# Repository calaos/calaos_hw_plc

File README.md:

# Intro

Calaos IO is an electronic board designed to controlled as many I/O as possible. It's intented to replace the wago IO modules in a house. It takes places in the electronic board.
Calaos IO is currently in design phase, and it's far to be complete

Look at calaos Wiki for more informations : http://www.calaos.fr/wiki/en/calaos_io_controller

This repository holds the documentation for the software and protocol parts

# doc

The doc foloder contains the state machine definitions and frame format.

# src/stm32

The src folder contains a prototype for an STM32 master on the RS485 bus
In order to build it, the gcc4mbed submodule must be initialized using 

    git submodule update --init
    
Then to fetch the toolchain:

    cd gcc4mbed
    ./linux_install
    
Note that the compiler should be added in your PATH to be used.

Finally go to the src folder and type

    make

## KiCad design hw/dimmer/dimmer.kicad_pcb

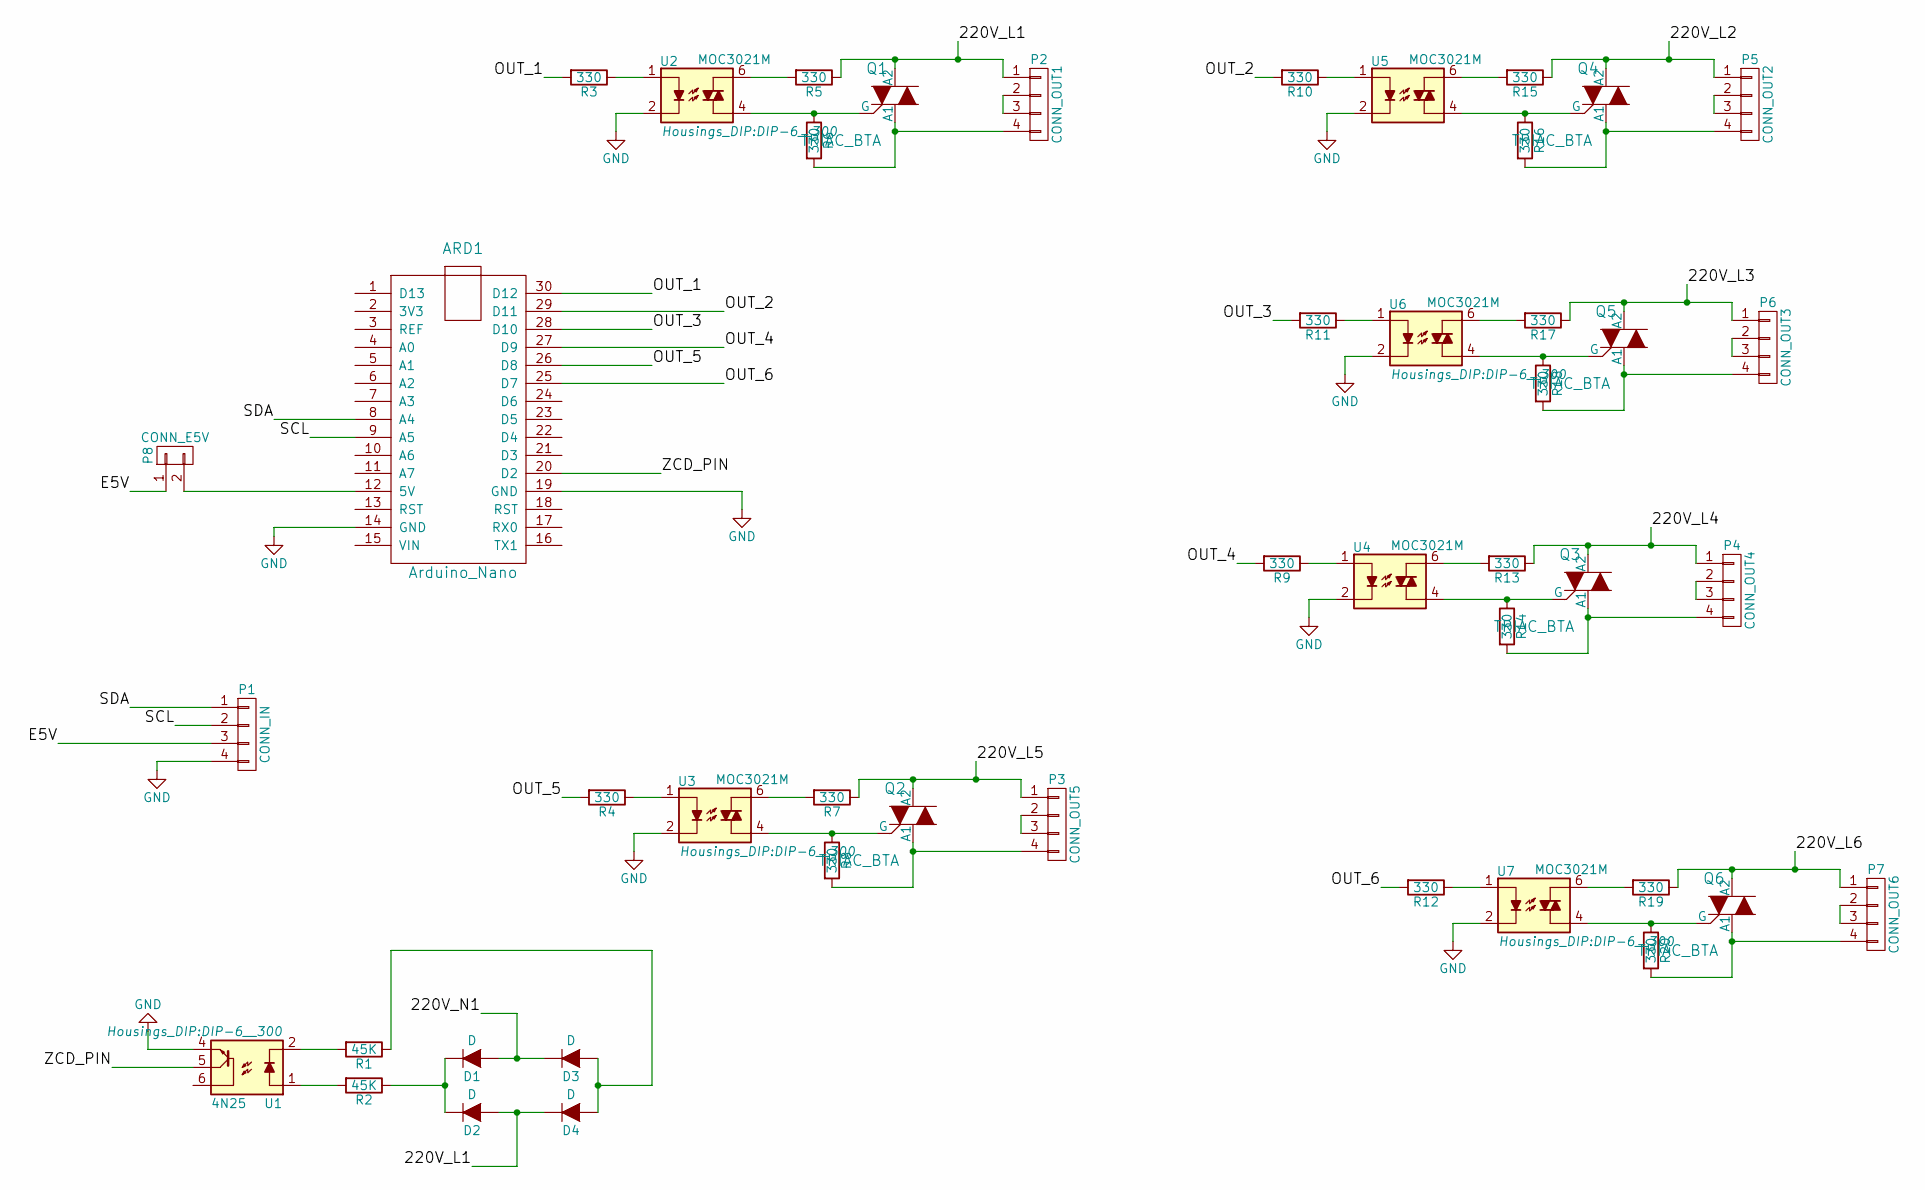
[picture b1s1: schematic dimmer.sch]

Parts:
ARD1: Arduino_Nano; arduino_nano_header
D1, D2, D3, D4: D; Diode_DO-35_SOD27_Horizontal_RM10
P1: CONN_IN; Pin_Header_Straight_1x04
P2: CONN_OUT1; mors_4p
P3: CONN_OUT5; mors_4p
P4: CONN_OUT4; mors_4p
P5: CONN_OUT2; mors_4p
P6: CONN_OUT3; mors_4p
P7: CONN_OUT6; mors_4p
P8: CONN_E5V; Pin_Header_Straight_1x02
Q1, Q2, Q3, Q4, Q5, Q6: TRIAC_BTA; TO-220
R1, R2: 45K; Resistor_Horizontal_RM10mm
R3, R4, R5, R6, R7, R8, R9, R10, R11, R12, R13, R14, R15, R16, R17, R18, R19, R20: 330; Resistor_Horizontal_RM10mm
U1: 4N25; DIP-6__300
U2, U3, U4, U5, U6, U7: MOC3021M; DIP-6__300

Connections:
/220V_L1: D2.1 (A), D4.2 (K), P2.1, Q1.2 (A2), R5.1
/220V_L2: P5.1, Q4.2 (A2), R15.1
/220V_L3: P6.1, Q5.2 (A2), R17.1
/220V_L4: P4.1, Q3.2 (A2), R13.1
/220V_L5: P3.1, Q2.2 (A2), R7.1
/220V_L6: P7.1, Q6.2 (A2), R19.1
/220V_N1: D1.1 (A), D3.2 (K)
/E5V: P1.3, P8.1
/OUT_1: ARD1.30 (D12), R3.2
/OUT_2: ARD1.29 (D11), R10.2
/OUT_3: ARD1.28 (D10), R11.2
/OUT_4: ARD1.27 (D9), R9.2
/OUT_5: ARD1.26 (D8), R4.2
/OUT_6: ARD1.25 (D7), R12.2
/SCL: ARD1.9 (A5), P1.2
/SDA: ARD1.8 (A4), P1.1
/ZCD_PIN: ARD1.20 (D2), U1.5
GND: ARD1.14 (GND), ARD1.19 (GND), P1.4, U1.4, U2.2, U3.2, U4.2, U5.2, U6.2, U7.2
unnamed: ARD1.12 (5V), P8.2
unnamed: D1.2 (K), D2.2 (K), R2.1
unnamed: D3.1 (A), D4.1 (A), R1.1
unnamed: P2.2, P2.3
unnamed: P2.4, Q1.3 (A1), R6.2
unnamed: P3.2, P3.3
unnamed: P3.4, Q2.3 (A1), R8.2
unnamed: P4.2, P4.3
unnamed: P4.4, Q3.3 (A1), R14.2
unnamed: P5.2, P5.3
unnamed: P5.4, Q4.3 (A1), R16.2
unnamed: P6.2, P6.3
unnamed: P6.4, Q5.3 (A1), R18.2
unnamed: P7.2, P7.3
unnamed: P7.4, Q6.3 (A1), R20.2
unnamed: Q1.1 (G), R6.1, U2.4
unnamed: Q2.1 (G), R8.1, U3.4
unnamed: Q3.1 (G), R14.1, U4.4
unnamed: Q4.1 (G), R16.1, U5.4
unnamed: Q5.1 (G), R18.1, U6.4
unnamed: Q6.1 (G), R20.1, U7.4
unnamed: R1.2, U1.2
unnamed: R2.2, U1.1
unnamed: R3.1, U2.1
unnamed: R4.1, U3.1
unnamed: R5.2, U2.6
unnamed: R7.2, U3.6
unnamed: R9.1, U4.1
unnamed: R10.1, U5.1
unnamed: R11.1, U6.1
unnamed: R12.1, U7.1
unnamed: R13.2, U4.6
unnamed: R15.2, U5.6
unnamed: R17.2, U6.6
unnamed: R19.2, U7.6

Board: 2 copper layers, 46 parts (0 on the bottom side), 53 nets, no tracks yet.

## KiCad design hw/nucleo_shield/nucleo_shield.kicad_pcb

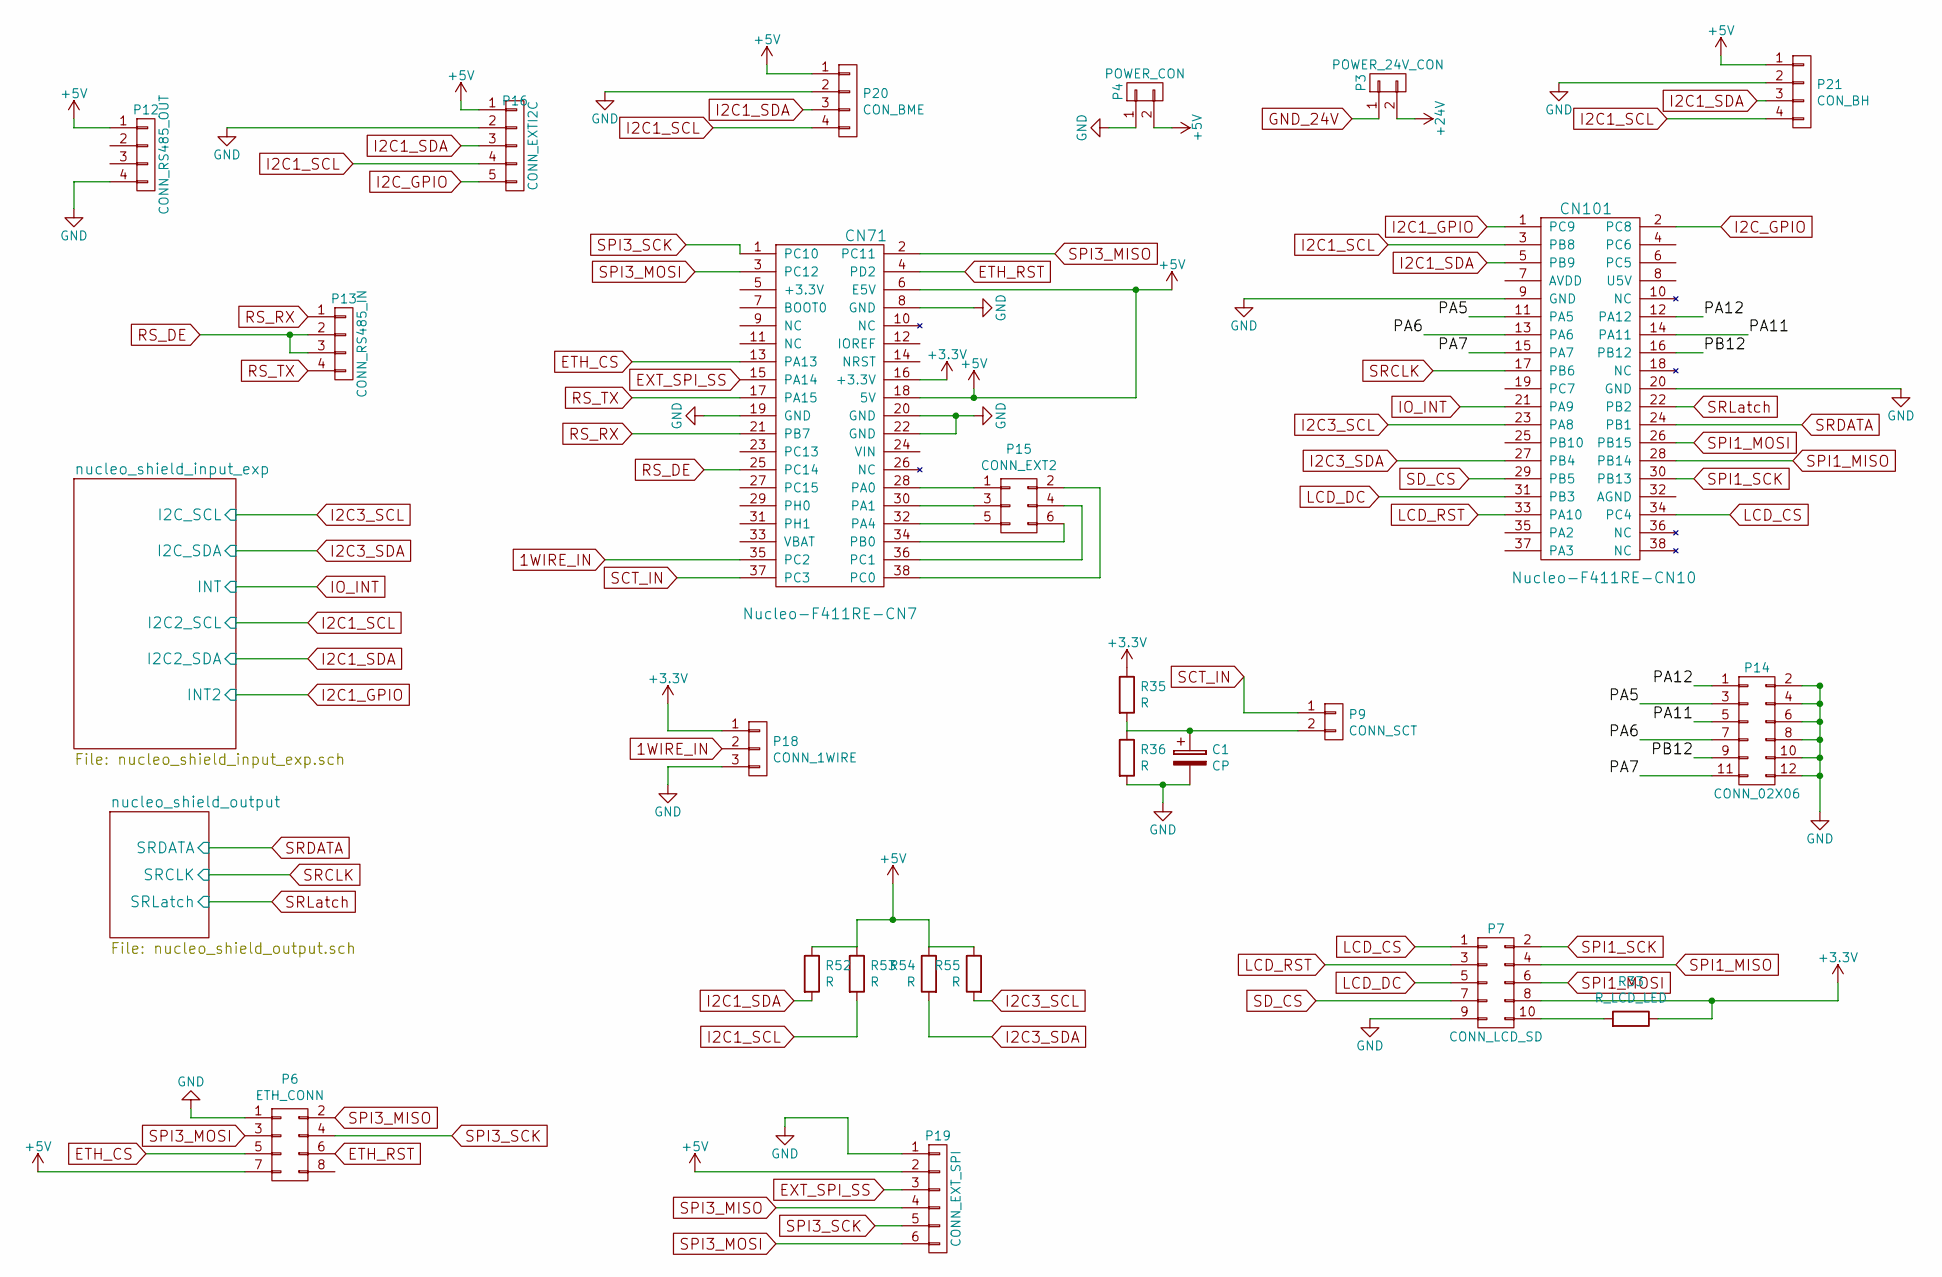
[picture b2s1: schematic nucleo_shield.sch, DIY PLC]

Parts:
C1: CP; C_Radial_D5_L11_P2
CN71: Nucleo-F411RE-CN7; Pin_Header_Straight_2x19
CN101: Nucleo-F411RE-CN10; Pin_Header_Straight_2x19
P3: POWER_24V_CON; mors_2p
P4: POWER_CON; mors_2p
P6: ETH_CONN; Pin_Header_Straight_2x04
P7: CONN_LCD_SD; Pin_Header_Straight_2x05
P9: CONN_SCT; Pin_Header_Straight_1x02
P12: CONN_RS485_OUT; Pin_Header_Straight_1x04
P13: CONN_RS485_IN; Pin_Header_Straight_1x04
P14: CONN_02X06; Pin_Header_Straight_2x06
P15: CONN_EXT2; Pin_Header_Straight_2x03
P16: CONN_EXTI2C; Pin_Header_Straight_1x05
P18: CONN_1WIRE; Pin_Header_Straight_1x03
P19: CONN_EXT_SPI; Pin_Header_Straight_1x06
P20: CON_BME; Pin_Header_Straight_1x04
P21: CON_BH; Pin_Header_Straight_1x04
R33: R_LCD_LED; R_0805_HandSoldering
R35, R36, R52, R53, R54, R55: R; R_0805_HandSoldering

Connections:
1WIRE_IN: CN71.35 (PC2), P18.2
+3V3: CN71.16 (+3.3V), P7.8, P18.1, R33.1, R35.1
+24V: P3.2; also elsewhere on the board
/PA5: CN101.11 (PA5), P14.3
/PA6: CN101.13 (PA6), P14.7
/PA7: CN101.15 (PA7), P14.11
/PA11: CN101.14 (PA11), P14.5
/PA12: CN101.12 (PA12), P14.1
/PB12: CN101.16 (PB12), P14.9
ETH_CS: CN71.13 (PA13), P6.5
ETH_RST: CN71.4 (PD2), P6.6
EXT_SPI_SS: CN71.15 (PA14), P19.3
GND: C1.2, CN71.8 (GND), CN71.19 (GND), CN71.20 (GND), CN71.22 (GND), CN101.9 (GND), CN101.20 (GND), P4.1, P6.1, P7.9, P12.4, P14.2, P14.4, P14.6, P14.8, P14.10, P14.12, P16.2, P18.3, P19.1, P20.2, P21.2, R36.2; also elsewhere on the board
GND_24V: P3.1; also elsewhere on the board
I2C1_GPIO: CN101.1 (PC9); also elsewhere on the board
I2C1_SCL: CN101.3 (PB8), P16.4, P20.4, P21.4, R53.2; also elsewhere on the board
I2C1_SDA: CN101.5 (PB9), P16.3, P20.3, P21.3, R52.2; also elsewhere on the board
I2C3_SCL: CN101.23 (PA8), R55.2; also elsewhere on the board
I2C3_SDA: CN101.27 (PB4), R54.2; also elsewhere on the board
I2C_GPIO: CN101.2 (PC8), P16.5
IO_INT: CN101.21 (PA9); also elsewhere on the board
LCD_CS: CN101.34 (PC4), P7.1
LCD_DC: CN101.31 (PB3), P7.5
LCD_RST: CN101.33 (PA10), P7.3
unnamed: C1.1, P9.2, R35.2, R36.1
unnamed: CN71.28 (PA0), P15.1
unnamed: CN71.30 (PA1), P15.3
unnamed: CN71.32 (PA4), P15.5
unnamed: CN71.34 (PB0), P15.6
unnamed: CN71.36 (PC1), P15.4
unnamed: CN71.38 (PC0), P15.2
unnamed: P7.10, R33.2
RS_DE: CN71.25 (PC14), P13.2, P13.3
RS_RX: CN71.21 (PB7), P13.1
RS_TX: CN71.17 (PA15), P13.4
SCT_IN: CN71.37 (PC3), P9.1
SD_CS: CN101.29 (PB5), P7.7
SPI1_MISO: CN101.28 (PB14), P7.4
SPI1_MOSI: CN101.26 (PB15), P7.6
SPI1_SCK: CN101.30 (PB13), P7.2
SPI3_MISO: CN71.2 (PC11), P6.2, P19.4
SPI3_MOSI: CN71.3 (PC12), P6.3, P19.6
SPI3_SCK: CN71.1 (PC10), P6.4, P19.5
SRCLK: CN101.17 (PB6); also elsewhere on the board
SRDATA: CN101.24 (PB1); also elsewhere on the board
SRLatch: CN101.22 (PB2); also elsewhere on the board
VCC: CN71.6 (E5V), CN71.18 (5V), P4.2, P6.7, P12.1, P16.1, P19.2, P20.1, P21.1, R52.1, R53.1, R54.1, R55.1; also elsewhere on the board

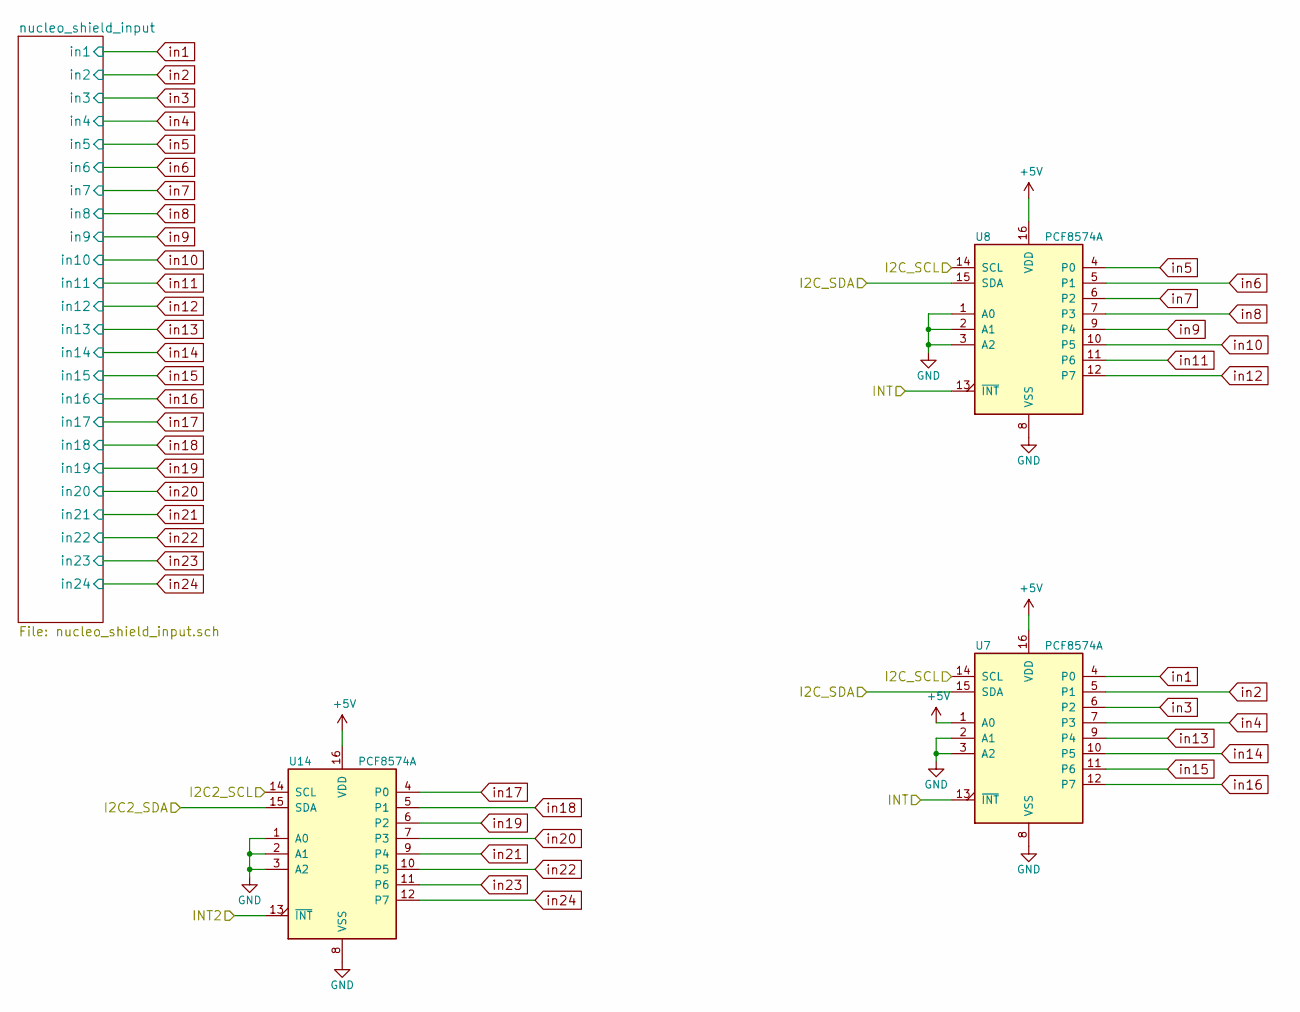
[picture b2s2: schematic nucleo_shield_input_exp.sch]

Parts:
U7, U8, U14: PCF8574A; DIP-16__300

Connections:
GND: U7.2 (A1), U7.3 (A2), U7.8 (VSS), U8.1 (A0), U8.2 (A1), U8.3 (A2), U8.8 (VSS), U14.1 (A0), U14.2 (A1), U14.3 (A2), U14.8 (VSS); also elsewhere on the board
I2C1_GPIO: U14.13 (~INT~); also elsewhere on the board
I2C1_SCL: U14.14 (SCL); also elsewhere on the board
I2C1_SDA: U14.15 (SDA); also elsewhere on the board
I2C3_SCL: U7.14 (SCL), U8.14 (SCL); also elsewhere on the board
I2C3_SDA: U7.15 (SDA), U8.15 (SDA); also elsewhere on the board
IO_INT: U7.13 (~INT~), U8.13 (~INT~); also elsewhere on the board
VCC: U7.1 (A0), U7.16 (VDD), U8.16 (VDD), U14.16 (VDD); also elsewhere on the board
in1: U7.4 (P0); also elsewhere on the board
in2: U7.5 (P1); also elsewhere on the board
in3: U7.6 (P2); also elsewhere on the board
in4: U7.7 (P3); also elsewhere on the board
in5: U8.4 (P0); also elsewhere on the board
in6: U8.5 (P1); also elsewhere on the board
in7: U8.6 (P2); also elsewhere on the board
in8: U8.7 (P3); also elsewhere on the board
in9: U8.9 (P4); also elsewhere on the board
in10: U8.10 (P5); also elsewhere on the board
in11: U8.11 (P6); also elsewhere on the board
in12: U8.12 (P7); also elsewhere on the board
in13: U7.9 (P4); also elsewhere on the board
in14: U7.10 (P5); also elsewhere on the board
in15: U7.11 (P6); also elsewhere on the board
in16: U7.12 (P7); also elsewhere on the board
in17: U14.4 (P0); also elsewhere on the board
in18: U14.5 (P1); also elsewhere on the board
in19: U14.6 (P2); also elsewhere on the board
in20: U14.7 (P3); also elsewhere on the board
in21: U14.9 (P4); also elsewhere on the board
in22: U14.10 (P5); also elsewhere on the board
in23: U14.11 (P6); also elsewhere on the board
in24: U14.12 (P7); also elsewhere on the board

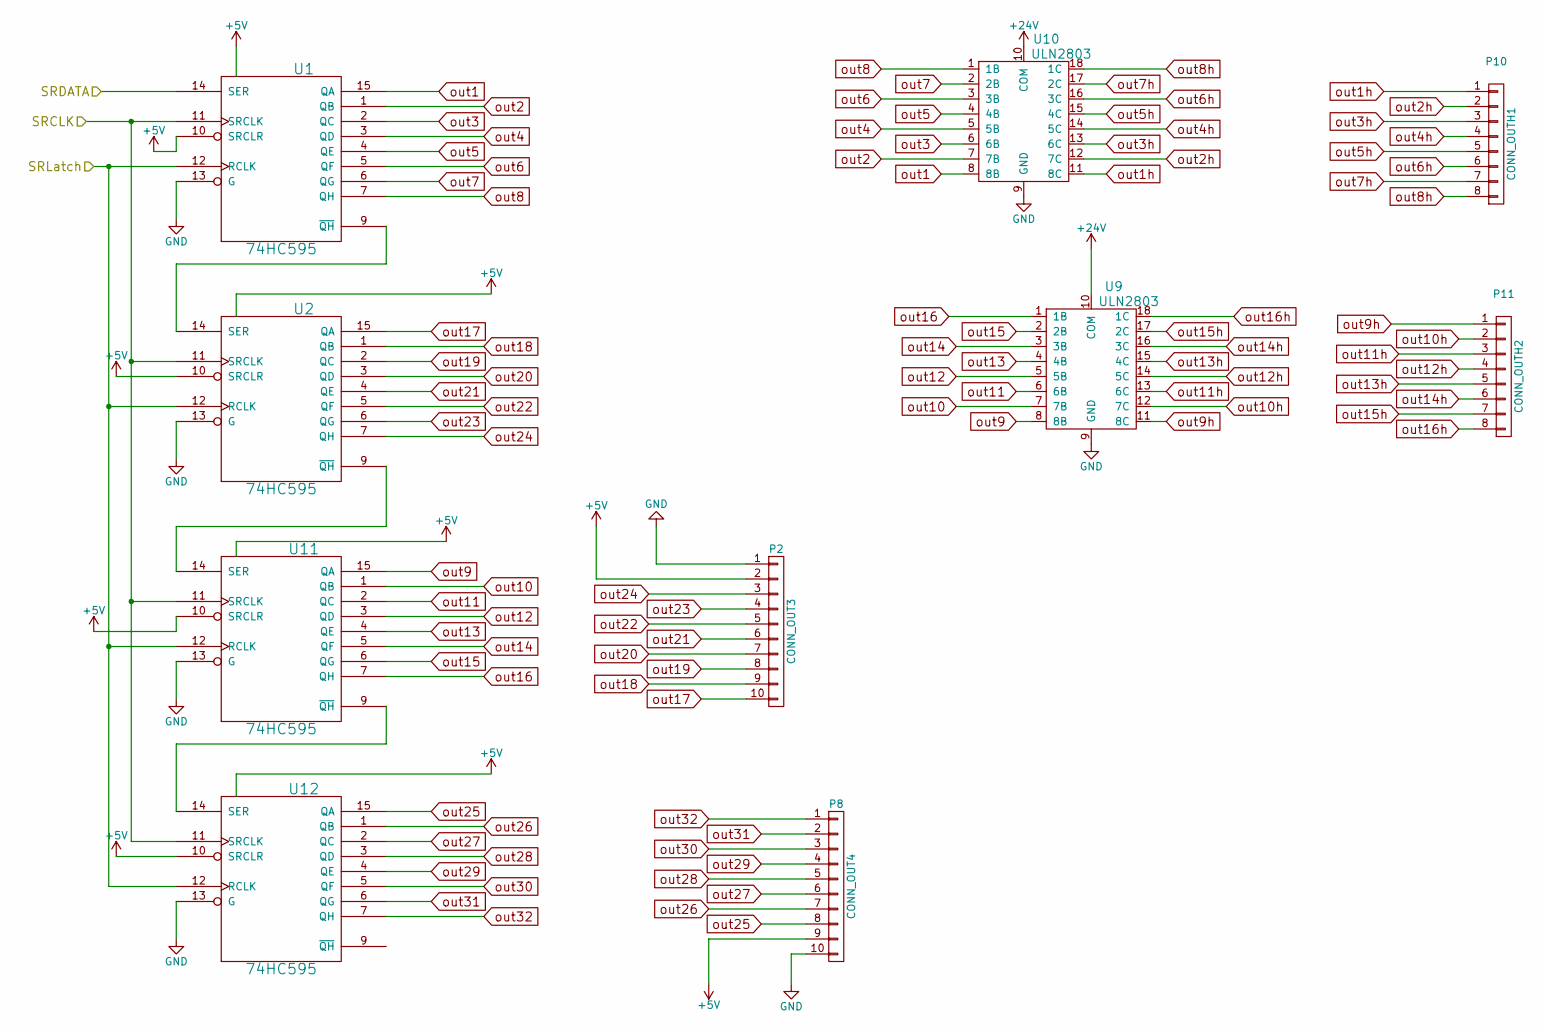
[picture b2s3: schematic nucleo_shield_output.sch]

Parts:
P2: CONN_OUT3; Pin_Header_Straight_1x10
P8: CONN_OUT4; Pin_Header_Straight_1x10
P10: CONN_OUTH1; mors_8p
P11: CONN_OUTH2; mors_8p
U1, U2, U11, U12: 74HC595; DIP-16__300
U9, U10: ULN2803; DIP-18__300

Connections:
+24V: U9.10 (COM), U10.10 (COM); also elsewhere on the board
GND: P2.1, P8.10, U1.8 (GND), U1.13 (G), U2.8 (GND), U2.13 (G), U9.9 (GND), U10.9 (GND), U11.8 (GND), U11.13 (G), U12.8 (GND), U12.13 (G); also elsewhere on the board
unnamed: U1.9 (~QH), U2.14 (SER)
unnamed: U11.9 (~QH), U12.14 (SER)
unnamed: U2.9 (~QH), U11.14 (SER)
SRCLK: U1.11 (SRCLK), U2.11 (SRCLK), U11.11 (SRCLK), U12.11 (SRCLK); also elsewhere on the board
SRDATA: U1.14 (SER); also elsewhere on the board
SRLatch: U1.12 (RCLK), U2.12 (RCLK), U11.12 (RCLK), U12.12 (RCLK); also elsewhere on the board
VCC: P2.2, P8.9, U1.10 (SRCLR), U1.16 (VCC), U2.10 (SRCLR), U2.16 (VCC), U11.10 (SRCLR), U11.16 (VCC), U12.10 (SRCLR), U12.16 (VCC); also elsewhere on the board
out1: U1.15 (QA), U10.8 (8B)
out1h: P10.1, U10.11 (8C)
out2: U1.1 (QB), U10.7 (7B)
out2h: P10.2, U10.12 (7C)
out3: U1.2 (QC), U10.6 (6B)
out3h: P10.3, U10.13 (6C)
out4: U1.3 (QD), U10.5 (5B)
out4h: P10.4, U10.14 (5C)
out5: U1.4 (QE), U10.4 (4B)
out5h: P10.5, U10.15 (4C)
out6: U1.5 (QF), U10.3 (3B)
out6h: P10.6, U10.16 (3C)
out7: U1.6 (QG), U10.2 (2B)
out7h: P10.7, U10.17 (2C)
out8: U1.7 (QH), U10.1 (1B)
out8h: P10.8, U10.18 (1C)
out9: U9.8 (8B), U11.15 (QA)
out9h: P11.1, U9.11 (8C)
out10: U9.7 (7B), U11.1 (QB)
out10h: P11.2, U9.12 (7C)
out11: U9.6 (6B), U11.2 (QC)
out11h: P11.3, U9.13 (6C)
out12: U9.5 (5B), U11.3 (QD)
out12h: P11.4, U9.14 (5C)
out13: U9.4 (4B), U11.4 (QE)
out13h: P11.5, U9.15 (4C)
out14: U9.3 (3B), U11.5 (QF)
out14h: P11.6, U9.16 (3C)
out15: U9.2 (2B), U11.6 (QG)
out15h: P11.7, U9.17 (2C)
out16: U9.1 (1B), U11.7 (QH)
out16h: P11.8, U9.18 (1C)
out17: P2.10, U2.15 (QA)
out18: P2.9, U2.1 (QB)
out19: P2.8, U2.2 (QC)
out20: P2.7, U2.3 (QD)
out21: P2.6, U2.4 (QE)
out22: P2.5, U2.5 (QF)
out23: P2.4, U2.6 (QG)
out24: P2.3, U2.7 (QH)
out25: P8.8, U12.15 (QA)
out26: P8.7, U12.1 (QB)
out27: P8.6, U12.2 (QC)
out28: P8.5, U12.3 (QD)
out29: P8.4, U12.4 (QE)
out30: P8.3, U12.5 (QF)
out31: P8.2, U12.6 (QG)
out32: P8.1, U12.7 (QH)

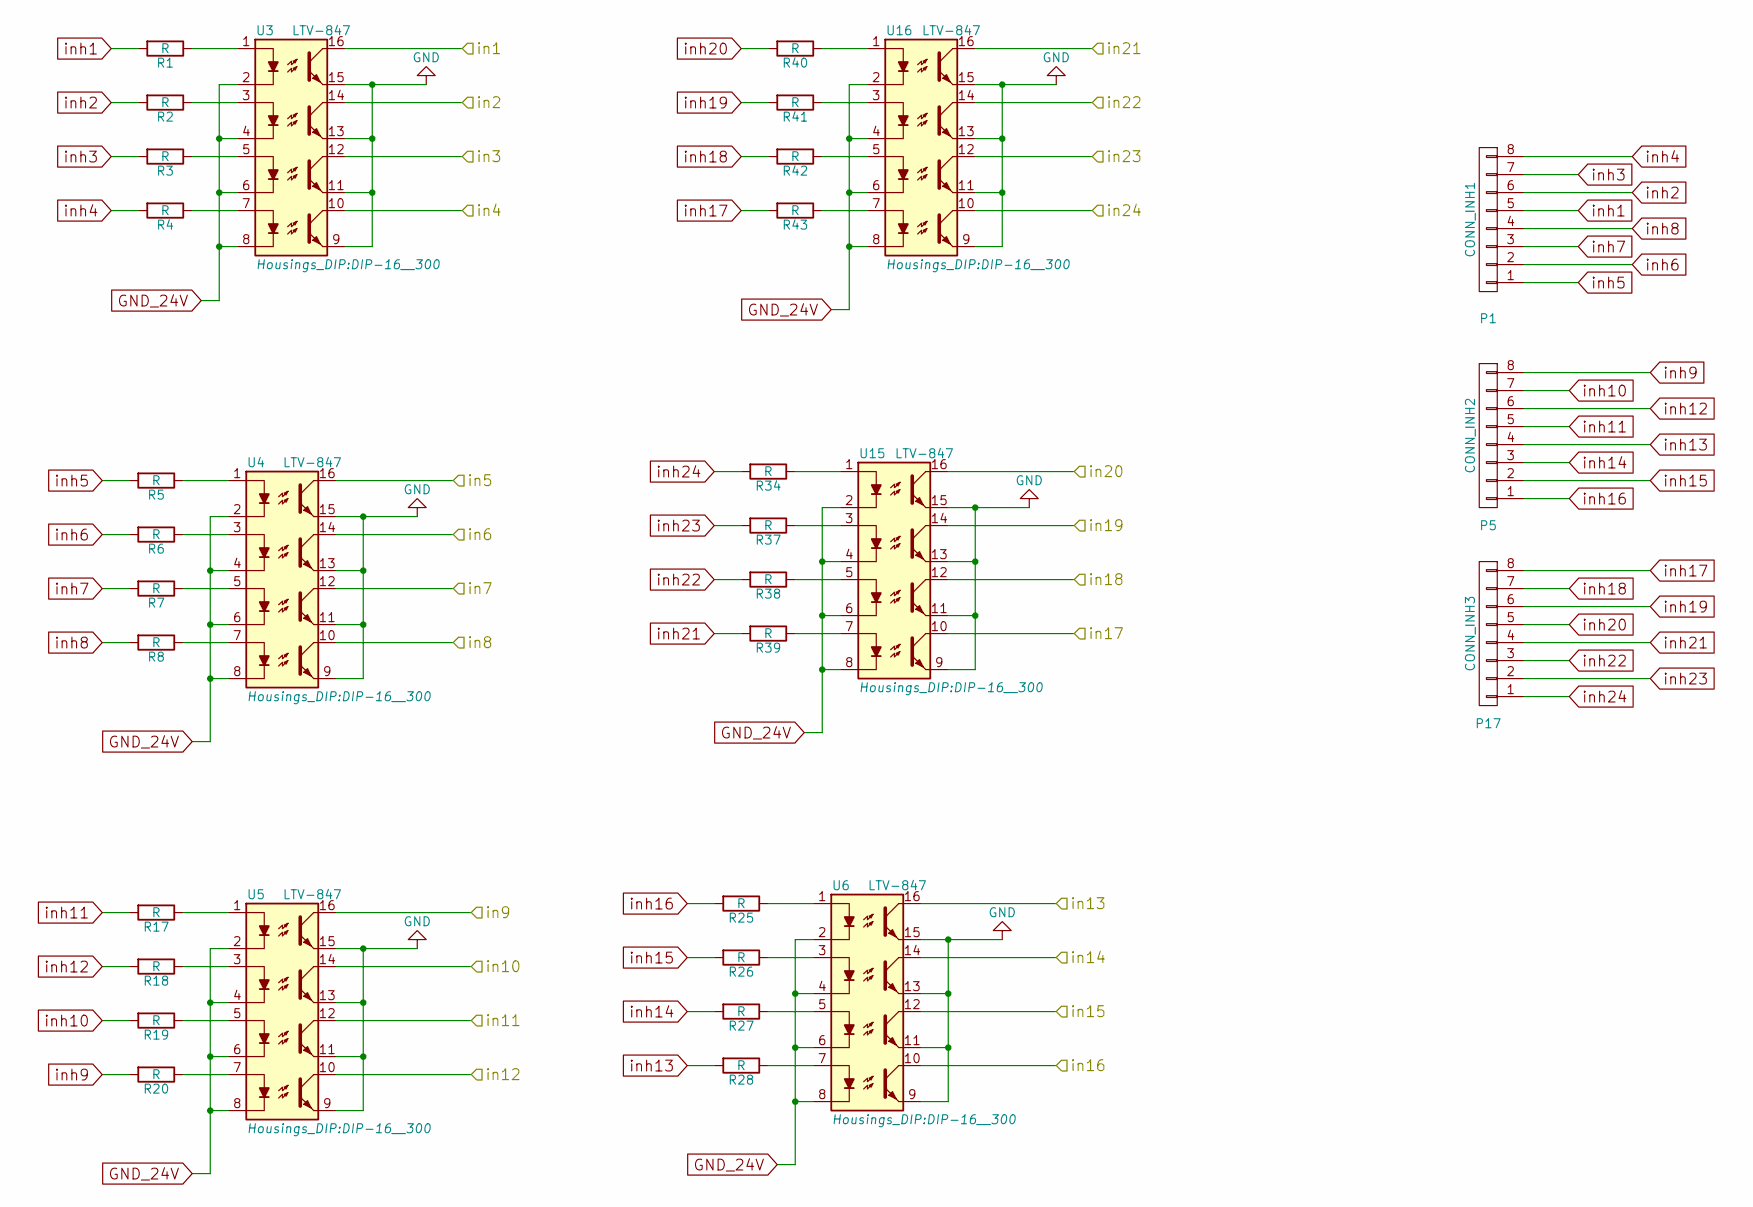
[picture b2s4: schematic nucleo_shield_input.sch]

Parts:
P1: CONN_INH1; mors_8p
P5: CONN_INH2; mors_8p
P17: CONN_INH3; mors_8p
R1, R2, R3, R4, R5, R6, R7, R8, R17, R18, R19, R20, R25, R26, R27, R28, R34, R37, R38, R39, R40, R41, R42, R43: R; R_0805_HandSoldering
U3, U4, U5, U6, U15, U16: LTV-847; DIP-16__300

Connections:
GND: U3.9, U3.11, U3.13, U3.15, U4.9, U4.11, U4.13, U4.15, U5.9, U5.11, U5.13, U5.15, U6.9, U6.11, U6.13, U6.15, U15.9, U15.11, U15.13, U15.15, U16.9, U16.11, U16.13, U16.15; also elsewhere on the board
GND_24V: U3.2, U3.4, U3.6, U3.8, U4.2, U4.4, U4.6, U4.8, U5.2, U5.4, U5.6, U5.8, U6.2, U6.4, U6.6, U6.8, U15.2, U15.4, U15.6, U15.8, U16.2, U16.4, U16.6, U16.8; also elsewhere on the board
unnamed: R1.1, U3.1
unnamed: R2.1, U3.3
unnamed: R3.1, U3.5
unnamed: R4.1, U3.7
unnamed: R5.1, U4.1
unnamed: R6.1, U4.3
unnamed: R7.1, U4.5
unnamed: R8.1, U4.7
unnamed: R17.1, U5.1
unnamed: R18.1, U5.3
unnamed: R19.1, U5.5
unnamed: R20.1, U5.7
unnamed: R25.1, U6.1
unnamed: R26.1, U6.3
unnamed: R27.1, U6.5
unnamed: R28.1, U6.7
unnamed: R34.1, U15.1
unnamed: R37.1, U15.3
unnamed: R38.1, U15.5
unnamed: R39.1, U15.7
unnamed: R40.1, U16.1
unnamed: R41.1, U16.3
unnamed: R42.1, U16.5
unnamed: R43.1, U16.7
in1: U3.16; also elsewhere on the board
in2: U3.14; also elsewhere on the board
in3: U3.12; also elsewhere on the board
in4: U3.10; also elsewhere on the board
in5: U4.16; also elsewhere on the board
in6: U4.14; also elsewhere on the board
in7: U4.12; also elsewhere on the board
in8: U4.10; also elsewhere on the board
in9: U5.16; also elsewhere on the board
in10: U5.14; also elsewhere on the board
in11: U5.12; also elsewhere on the board
in12: U5.10; also elsewhere on the board
in13: U6.16; also elsewhere on the board
in14: U6.14; also elsewhere on the board
in15: U6.12; also elsewhere on the board
in16: U6.10; also elsewhere on the board
in17: U15.10; also elsewhere on the board
in18: U15.12; also elsewhere on the board
in19: U15.14; also elsewhere on the board
in20: U15.16; also elsewhere on the board
in21: U16.16; also elsewhere on the board
in22: U16.14; also elsewhere on the board
in23: U16.12; also elsewhere on the board
in24: U16.10; also elsewhere on the board
inh1: P1.5, R1.2
inh2: P1.6, R2.2
inh3: P1.7, R3.2
inh4: P1.8, R4.2
inh5: P1.1, R5.2
inh6: P1.2, R6.2
inh7: P1.3, R7.2
inh8: P1.4, R8.2
inh9: P5.8, R20.2
inh10: P5.7, R19.2
inh11: P5.5, R17.2
inh12: P5.6, R18.2
inh13: P5.4, R28.2
inh14: P5.3, R27.2
inh15: P5.2, R26.2
inh16: P5.1, R25.2
inh17: P17.8, R43.2
inh18: P17.7, R42.2
inh19: P17.6, R41.2
inh20: P17.5, R40.2
inh21: P17.4, R39.2
inh22: P17.3, R38.2
inh23: P17.2, R37.2
inh24: P17.1, R34.2

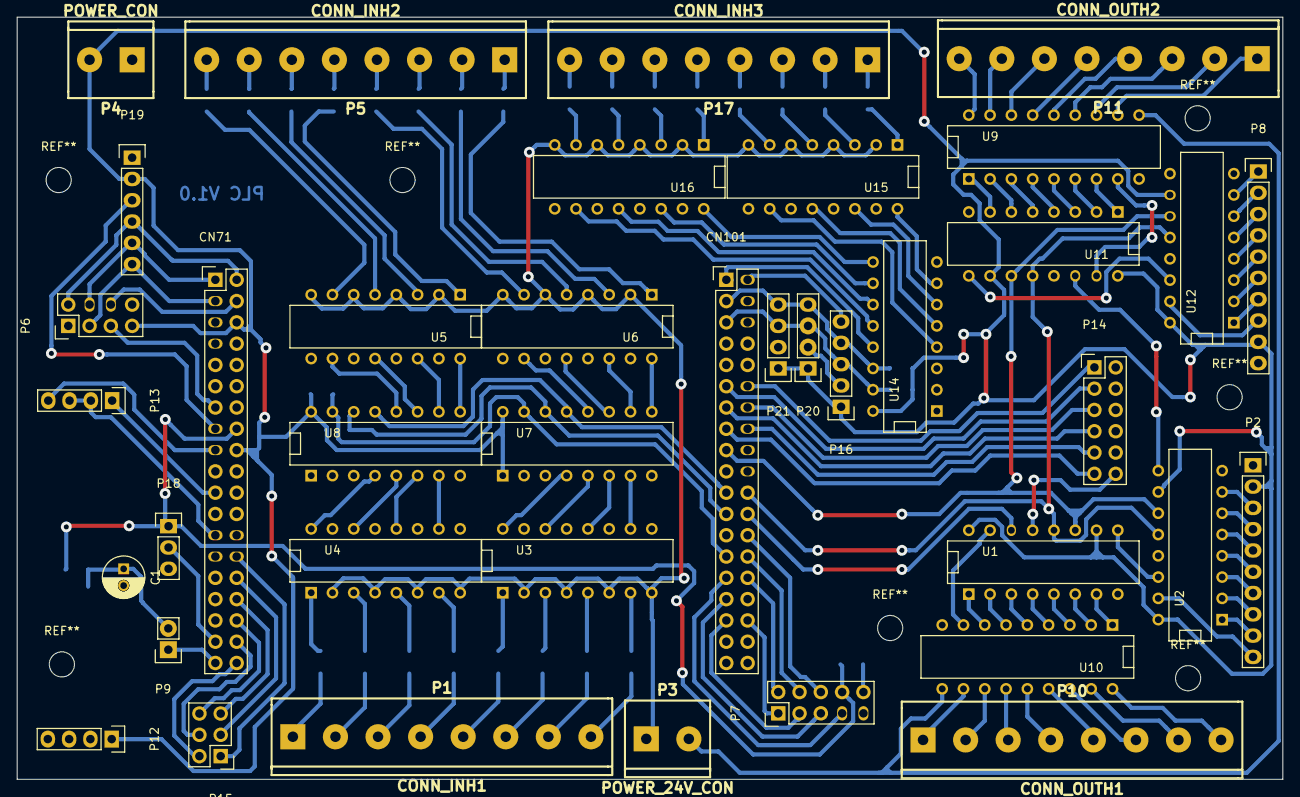
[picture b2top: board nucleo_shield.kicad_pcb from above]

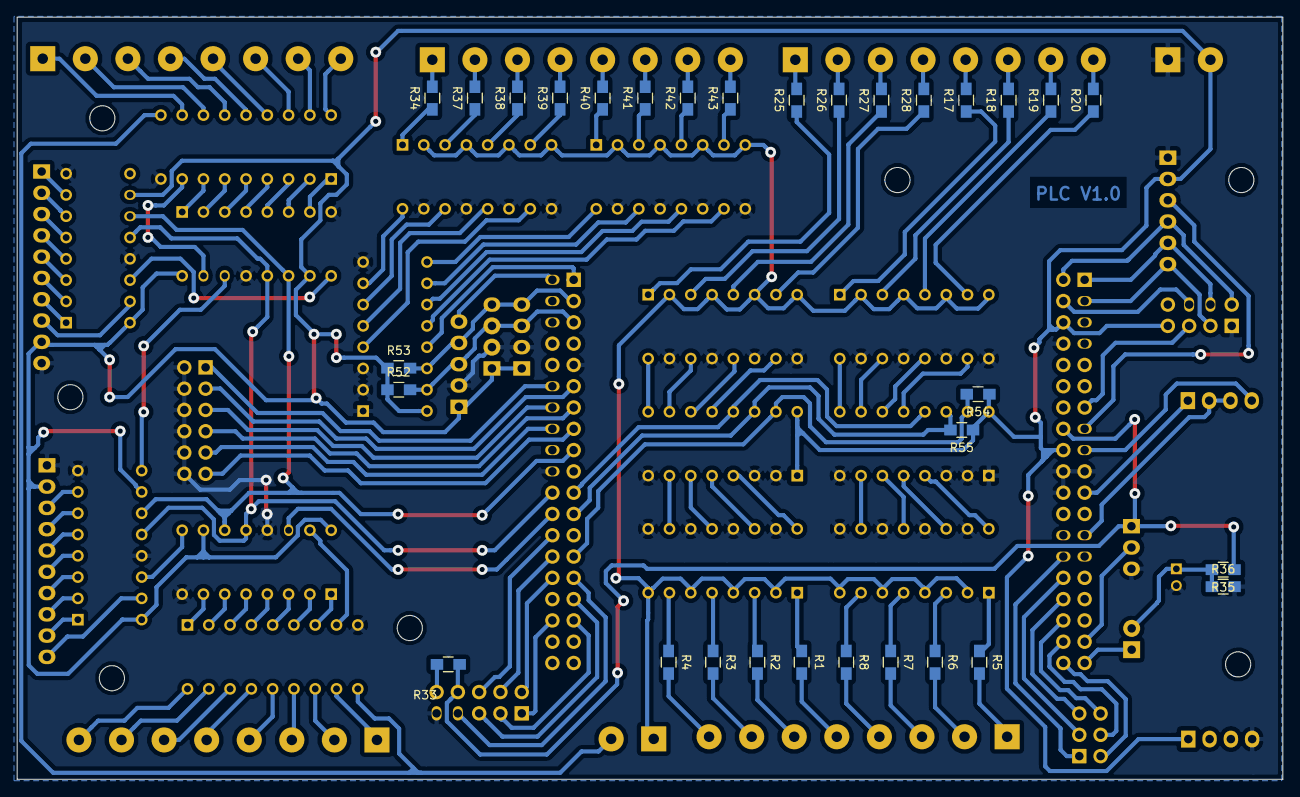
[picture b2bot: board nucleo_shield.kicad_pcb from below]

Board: 2 copper layers, 151.0 x 90.9 mm, 70 parts (31 on the bottom side), 170 nets.

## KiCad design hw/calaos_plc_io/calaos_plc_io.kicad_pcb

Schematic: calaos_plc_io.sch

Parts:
C1, C2: 20pF; C_0603
C3, C4: 0.33uF; C_0603
C5, C6: 0.1uF; C_0603
C7, C10: 10uF; C_0603
C8, C9, C11, C12, C13, C14, C15: 100nF; C_0603
CON1, CON2: TerminalBlock; Terminalblock_1708084
D1: LED; LED-0603
JP1: Jumper_NO_Small; SolderWirePad_2x_0-8mmDrill
P1: SERIAL_DBG; Pin_Header_Straight_1x04
P2: CONN_01X06; Pin_Header_Straight_1x06
P4: CONN_01X04; Terminalbloc_1726040
R1: 1k; R_0603
R2: 510; R_0603
R99: 120; R_0603
U1: LM7824CT; TO-220; Mouser Ref 512-LM7824CT
U2: LM7805CT; TO-220; Mouser Ref 512-LM7805CT
U3: LD1117S33TR; SOT-223; Mouser Ref 926-LM1117MPX3.3NOPB
U4: STM32F105R8; LQFP-64_10x10mm_Pitch0.5mm
U5: MCP2551-I/SN; SOIC-8_3.9x4.9mm_Pitch1.27mm
Y1: 8MHz; crystal_FA238-TSX3225

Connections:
+5V: C6.1, C7.1, U2.3 (OUT), U3.3; also elsewhere on the board
+24V: C5.1, P4.1, U1.3 (OUT); also elsewhere on the board
/CANH: P4.2, U5.7
/CANL: P4.3, R99.2, U5.6
/Inputs-1/DI_01: CON2.1; also elsewhere on the board
/Inputs-1/DI_02: CON2.2; also elsewhere on the board
/Inputs-1/DI_03: CON2.3; also elsewhere on the board
/Inputs-1/DI_04: CON2.4; also elsewhere on the board
/Inputs-1/DI_05: CON2.5; also elsewhere on the board
/Inputs-1/DI_06: CON2.6; also elsewhere on the board
/Inputs-1/DI_07: CON2.7; also elsewhere on the board
/Inputs-1/DI_08: CON2.8; also elsewhere on the board
/Inputs-1/DI_09: CON2.9; also elsewhere on the board
/Inputs-1/DI_10: CON2.10; also elsewhere on the board
/Inputs-1/DI_11: CON2.11; also elsewhere on the board
/Inputs-1/DI_12: CON2.12; also elsewhere on the board
/Inputs-1/DI_13: CON2.13; also elsewhere on the board
/Inputs-1/DI_14: CON2.14; also elsewhere on the board
/Inputs-1/DI_15: CON2.15; also elsewhere on the board
/Inputs-1/DI_16: CON2.16; also elsewhere on the board
/Inputs-1/DO_01: CON1.1; also elsewhere on the board
/Inputs-1/DO_02: CON1.2; also elsewhere on the board
/Inputs-1/DO_03: CON1.3; also elsewhere on the board
/Inputs-1/DO_04: CON1.4; also elsewhere on the board
/Inputs-1/DO_05: CON1.5; also elsewhere on the board
/Inputs-1/DO_06: CON1.6; also elsewhere on the board
/Inputs-1/DO_07: CON1.7; also elsewhere on the board
/Inputs-1/DO_08: CON1.8; also elsewhere on the board
/Inputs-1/DO_09: CON1.9; also elsewhere on the board
/Inputs-1/DO_10: CON1.10; also elsewhere on the board
/Inputs-1/DO_11: CON1.11; also elsewhere on the board
/Inputs-1/DO_12: CON1.12; also elsewhere on the board
/Inputs-1/DO_13: CON1.13; also elsewhere on the board
/Inputs-1/DO_14: CON1.14; also elsewhere on the board
/Inputs-1/DO_15: CON1.15; also elsewhere on the board
/Inputs-1/DO_16: CON1.16; also elsewhere on the board
/Inputs-1/O_0: U4.8 (PC0/ADC12_IN10); also elsewhere on the board
/Inputs-1/O_1: U4.9 (PC1/ADC12_IN11); also elsewhere on the board
/Inputs-1/O_2: U4.10 (PC2/ADC12_IN12); also elsewhere on the board
/Inputs-1/O_3: U4.11 (PC3/ADC12_IN13); also elsewhere on the board
/Inputs-1/O_4: U4.24 (PC4/ADC12_IN14); also elsewhere on the board
/Inputs-1/O_5: U4.25 (PC5/ADC12_IN15); also elsewhere on the board
/Inputs-1/O_6: U4.37 (PC6/I2S2_MCK); also elsewhere on the board
/Inputs-1/O_7: U4.38 (PC7/I2S3_MCK); also elsewhere on the board
/Inputs-1/O_8: U4.39 (PC8); also elsewhere on the board
/Inputs-1/O_9: U4.40 (PC9); also elsewhere on the board
/Inputs-1/O_10: U4.51 (PC10/UART4_TX); also elsewhere on the board
/Inputs-1/O_11: U4.52 (PC11/UART4_RX); also elsewhere on the board
/Inputs-1/O_12: U4.53 (PC12/UART5_TX); also elsewhere on the board
/Inputs-1/O_13: U4.2 (PC13/TAMPER_RTC); also elsewhere on the board
/Inputs-1/O_14: U4.3 (PC14/OSC32_IN); also elsewhere on the board
/Inputs-1/O_15: U4.4 (PC15/OSC32_OUT); also elsewhere on the board
CAN_RX: U4.44 (USART1_CTS/CAN1_RX/TIM1_CH4/OTG_FS_DM/P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), U5.4
CAN_TX: U4.45 (USART1_RTS/OTG_FS_DP/CAN1_TX/TIM1_ETR/P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), U5.1
DBG_RX: P1.3, U4.43 (USART1_RX/TIM1_CH3/OTG_FS_ID/PA10)
DBG_TX: P1.2, U4.42 (USART1_TX/TIM1_CH2/OTG_FS_VBUS/PA9)
GND: C1.2, C2.2, C3.2, C4.2, C5.2, C6.2, C7.2, C8.2, C9.2, C10.2, C11.2, C12.2, C13.2, C14.2, C15.2, D1.1 (A), P1.1, P2.3, P4.4, R1.2, U1.2 (GND), U2.2 (GND), U3.1, U4.12 (VSSA), U4.18 (VSS), U4.31 (VSS), U4.47 (VSS), U4.60 (BOOT0), U4.63 (VSS), U5.2; also elsewhere on the board
NRST: P2.5, U4.7 (~NRST)
unnamed: C1.1, U4.5 (OSC_IN), Y1.1
unnamed: C2.1, U4.6 (OSC_OUT), Y1.2
unnamed: D1.2 (K), R2.2
unnamed: JP1.1, R99.1
unnamed: R1.1, U5.8
unnamed: R2.1, U4.50 (JTDI/SPI3_NSS/I2S3_WS/PA15)
SWCLK: P2.2, U4.49 (JTCK/SWCLK/PA14)
SWDIO: P2.4, U4.46 (JTMS/SWDIO/PA13)
VIN: C3.1, C4.1, U1.1 (IN), U2.1 (IN)

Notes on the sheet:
Indicator LED
